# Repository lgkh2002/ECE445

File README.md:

# ECE445

This is the Git repository for the JargonJolt ECE445 project by Daniel Chamoun, Luke Hartmann, and Nan Kang.

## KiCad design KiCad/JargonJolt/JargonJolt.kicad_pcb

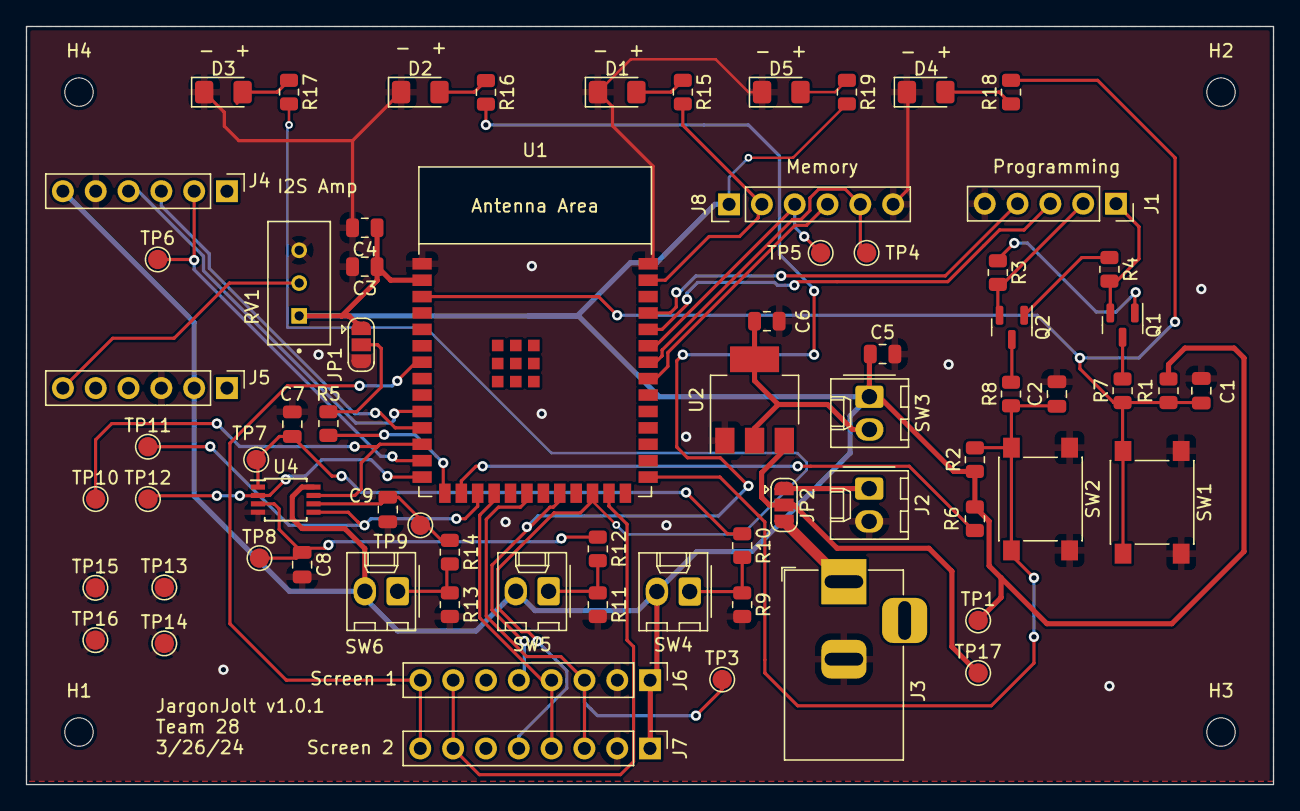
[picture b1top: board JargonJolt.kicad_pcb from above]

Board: 2 copper layers, 96.5 x 58.7 mm, 75 parts (0 on the bottom side), 47 nets.

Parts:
C1, C2, C3, C5, C6: 1u; C_0805_2012Metric
C4: 0.1u; C_0805_2012Metric
C7, C8, C9: 0.1uF; C_0805_2012Metric
D1, D2, D3, D4, D5: LED; LED_1206_3216Metric_Pad1.42x1.75mm_HandSolder
H1, H2, H3, H4: MountingHole; MountingHole_2.2mm_M2
J1: Conn_01x05; PinSocket_1x05_P2.54mm_Vertical
J2: Conn_01x02; Molex_KK-254_AE-6410-02A_1x02_P2.54mm_Vertical
J3: Conn_01x02; BarrelJack_Horizontal
J4, J5, J8: Conn_01x06; PinHeader_1x06_P2.54mm_Vertical
J6, J7: Conn_01x08; PinHeader_1x08_P2.54mm_Vertical
JP1, JP2: SolderJumper_3_Open; SolderJumper-3_P1.3mm_Open_RoundedPad1.0x1.5mm
Q1, Q2: SS8050-G; SOT-23
R1, R2: 100k; R_0805_2012Metric
R3, R4, R7, R8: 10k; R_0805_2012Metric
R5, R6, R10, R12, R14: 1k; R_0805_2012Metric
R9, R11, R13: 1M; R_0805_2012Metric
R15, R16, R17, R18, R19: R; R_0805_2012Metric
RV1: 100k_Potentiometer; TRIM_3296W-1-104LF
SW1, SW2: SW_Push; SW_Push_1P1T_NO_6x6mm_H9.5mm
SW3: SW_DIP_x01; Molex_KK-254_AE-6410-02A_1x02_P2.54mm_Vertical
SW4, SW5, SW6: SW_Push; Molex_KK-254_AE-6410-02A_1x02_P2.54mm_Vertical
TP1, TP3, TP4, TP5, TP6, TP7, TP8, TP9, TP10, TP11, TP12, TP13, TP14, TP15, TP16, TP17: TestPoint; TestPoint_Pad_D1.5mm
U1: ESP32-S3-WROOM-1-N16R2; ESP32-S3-WROOM-1
U2: ADP3339; SOT-223-3_TabPin2
U4: 74LVC3G17DP_125; TSSOP-8_3x3mm_P0.65mm

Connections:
+3.3V: C6.1, SW3.2, U2.2 (VO)
+3.3VA: C3.1, C4.1, C5.1, J4.6, J5.2, J6.1, J7.1, J8.1, JP1.1 (A), R1.1, R2.1, R6.1, R19.2, RV1.1, SW3.1, SW4.2, SW5.2, SW6.2, TP1.1, U1.2 (3V3), U4.8 (VCC)
+12V: J3.1, JP2.3 (B)
/MCU/BUSY: J6.8, J7.8, U1.7 (IO7)
/MCU/BUTTON1: TP10.1, U1.12 (IO8), U4.7 (1Y)
/MCU/BUTTON2: TP11.1, U1.17 (IO9), U4.5 (2Y)
/MCU/BUTTON3: TP12.1, U1.14 (IO20), U4.2 (3Y)
/MCU/CHIP_PU: C1.1, R1.2, R7.1, R18.2, SW1.2, U1.3 (EN)
/MCU/CS0: J8.2, R15.2, U1.39 (IO1)
/MCU/CS1: J6.5, R16.2, U1.22 (IO14)
/MCU/CS2: J7.5, R17.2, U1.24 (IO47)
/MCU/DTR: J1.2, Q2.2 (E), R3.2
/MCU/GPIO0_STRAP: C2.1, R2.2, R8.1, SW2.2, U1.27 (IO0)
/MCU/GPIO3_STRAP: R5.2, U1.15 (IO3)
/MCU/GPIO46_STRAP: R6.2, U1.16 (IO46)
/MCU/HSPI_MOSI: J6.3, J7.3, TP3.1, U1.20 (IO12)
/MCU/HSPI_SCLK: J6.4, J7.4, U1.18 (IO10)
/MCU/I2S_BCLK: J4.3, U1.11 (IO18)
/MCU/I2S_DATA: J4.2, TP6.1, U1.13 (IO19)
/MCU/I2S_LRCLK: J4.4, U1.10 (IO17)
/MCU/RST: J6.7, J7.7, U1.25 (IO48)
/MCU/RTS: J1.1, Q1.2 (E), R4.2
/MCU/Rx: J1.4, U1.37 (TXD0)
/MCU/Tx: J1.3, U1.36 (RXD0)
/MCU/VSPI_MISO: J8.5, TP4.1, U1.34 (IO41)
/MCU/VSPI_MOSI: J8.3, TP5.1, U1.35 (IO42)
/MCU/VSPI_SCLK: J8.4, U1.33 (IO40)
/Power/+3.7V: J2.1, JP2.1 (A)
/Power/P_in: JP2.2 (C), TP17.1, U2.3 (VI)
GND: C1.2, C2.2, C3.2, C4.2, C5.2, C6.2, C7.2, C8.2, C9.2, D1.1 (K), D2.1 (K), D3.1 (K), D4.1 (K), D5.1 (K), J1.5, J2.2, J3.2, J4.5, J5.3, J6.2, J7.2, J8.6, JP1.3 (B), R9.2, R11.2, R13.2, RV1.3, SW1.1, SW2.1, TP13.1, TP14.1, TP15.1, TP16.1, U1.1 (GND), U1.40 (GND), U2.1 (GND), U4.4 (GND)
unnamed: D1.2 (A), R15.1
unnamed: D2.2 (A), R16.1
unnamed: D3.2 (A), R17.1
unnamed: D4.2 (A), R18.1
unnamed: D5.2 (A), R19.1
unnamed: J5.6, RV1.2
unnamed: JP1.2 (C), R5.1
unnamed: Q1.1 (B), R3.1
unnamed: Q1.3 (C), R7.2
unnamed: Q2.1 (B), R4.1
unnamed: Q2.3 (C), R8.2
unnamed: R9.1, R10.2, SW4.1
unnamed: R11.1, R12.2, SW5.1
unnamed: R13.1, R14.2, SW6.1
unnamed: C7.1, R10.1, TP7.1, U4.1 (1A)
unnamed: C8.1, R12.1, TP8.1, U4.3 (2A)
unnamed: C9.1, R14.1, TP9.1, U4.6 (3A)

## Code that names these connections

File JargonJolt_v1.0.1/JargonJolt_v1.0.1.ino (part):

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#define hcs 14
#define hcs2 47

#define button1 8
#define button2 9
#define button3 20

#define I2S_DOUT      19
#define I2S_BCLK      18
#define I2S_LRC       17

#define WORDSPERROW 50
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
  //inputs
  pinMode(7, INPUT); //BUSY
  pinMode(button1, INPUT); //BUTTON1
  pinMode(button2, INPUT); //BUTTON2
  pinMode(button3, INPUT); //BUTTON3
  
  //outputs

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  pinMode(47, OUTPUT); //CS2
  pinMode(48, OUTPUT); //RST

  pinMode(17, OUTPUT); //I2S_LRCLK
  pinMode(18, OUTPUT); //I2S_BCLK
  pinMode(19, OUTPUT); //I2S_DATA

  pinMode(8,INPUT); //BUTTON1



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    Serial.println(" CONNECTED");
  }

  audio.setPinout(I2S_BCLK, I2S_LRC, I2S_DOUT);
  audio.setVolume(21); // default 0...21
}

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
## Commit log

2024-02-01 testing git repo
2024-02-01 test git
2024-02-01 test2
2024-02-02 ssh setup
2024-02-02 fixed
2024-02-06 Formatting git repo
2024-02-16 added specific esp32 module into KiCad
2024-02-16 added jargonjolt library
2024-02-19 began working on schematic
2024-02-21 updated notebook
2024-02-22 worked on pinout
2024-02-22 update notebook 2/22/2024
2024-02-28 worked on schematic
2024-03-01 added i2s schematic
2024-03-01 added sd module + fixed CS pins
2024-03-02 added more footprints
2024-03-02 add demo code for 3.52inch screen
2024-03-02 Add e-paper doc, add software for image processing
2024-03-04 add SD card code
2024-03-04 PCB first revision
2024-03-05 audit approved
2024-03-24 changed barrel connector to have proper pinout
2024-03-26 added test leds
2024-03-26 added 3.3v test led
2024-03-26 v1.0.1 audit approved
2024-03-29 updated lab notebook
2024-04-02 updated notebook -LH
2024-04-05 code
2024-04-07 SD CARD WORKSSSSSS
2024-04-07 lukegh2
2024-04-08 update esp screen code
2024-04-08 update folder name
2024-04-08 add arduino code for the screen
2024-04-10 upload esp32 code version for the screen
2024-04-10 began coding main loop code
2024-04-13 waveshare screen working
2024-04-13 main runtime code
2024-04-13 adding libraries for waveshare code
2024-04-13 adding libraries
2024-04-14 word wrap in esp32
2024-04-15 worked on main code, added fully workign drawtext
2024-04-15 add draw wrap text function
2024-04-16 made dummy flashcard set, updated notebook
2024-04-17 added flashcard reading and displaying basics
2024-04-17 dual screen support added
2024-04-18 display pet with 5 different emotion completed
2024-04-18 add drawpet code
2024-04-18 added time support
2024-04-18 bug fixes
2024-04-22 rotate image
2024-04-22 add pet status
2024-04-23 pet health
2024-04-23 audio worksssssss
2024-04-23 final demo commit
2024-04-26 update notebook
2024-04-30 Update README.md
    p1
2024-05-02 insert picture in notebook
2024-05-02 update nankang's notebook
2024-05-02 insert more images
2024-05-02 rename notebook
